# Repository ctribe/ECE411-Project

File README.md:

The nocLock
==============

A secret knock detector for you to hide your everyday items!

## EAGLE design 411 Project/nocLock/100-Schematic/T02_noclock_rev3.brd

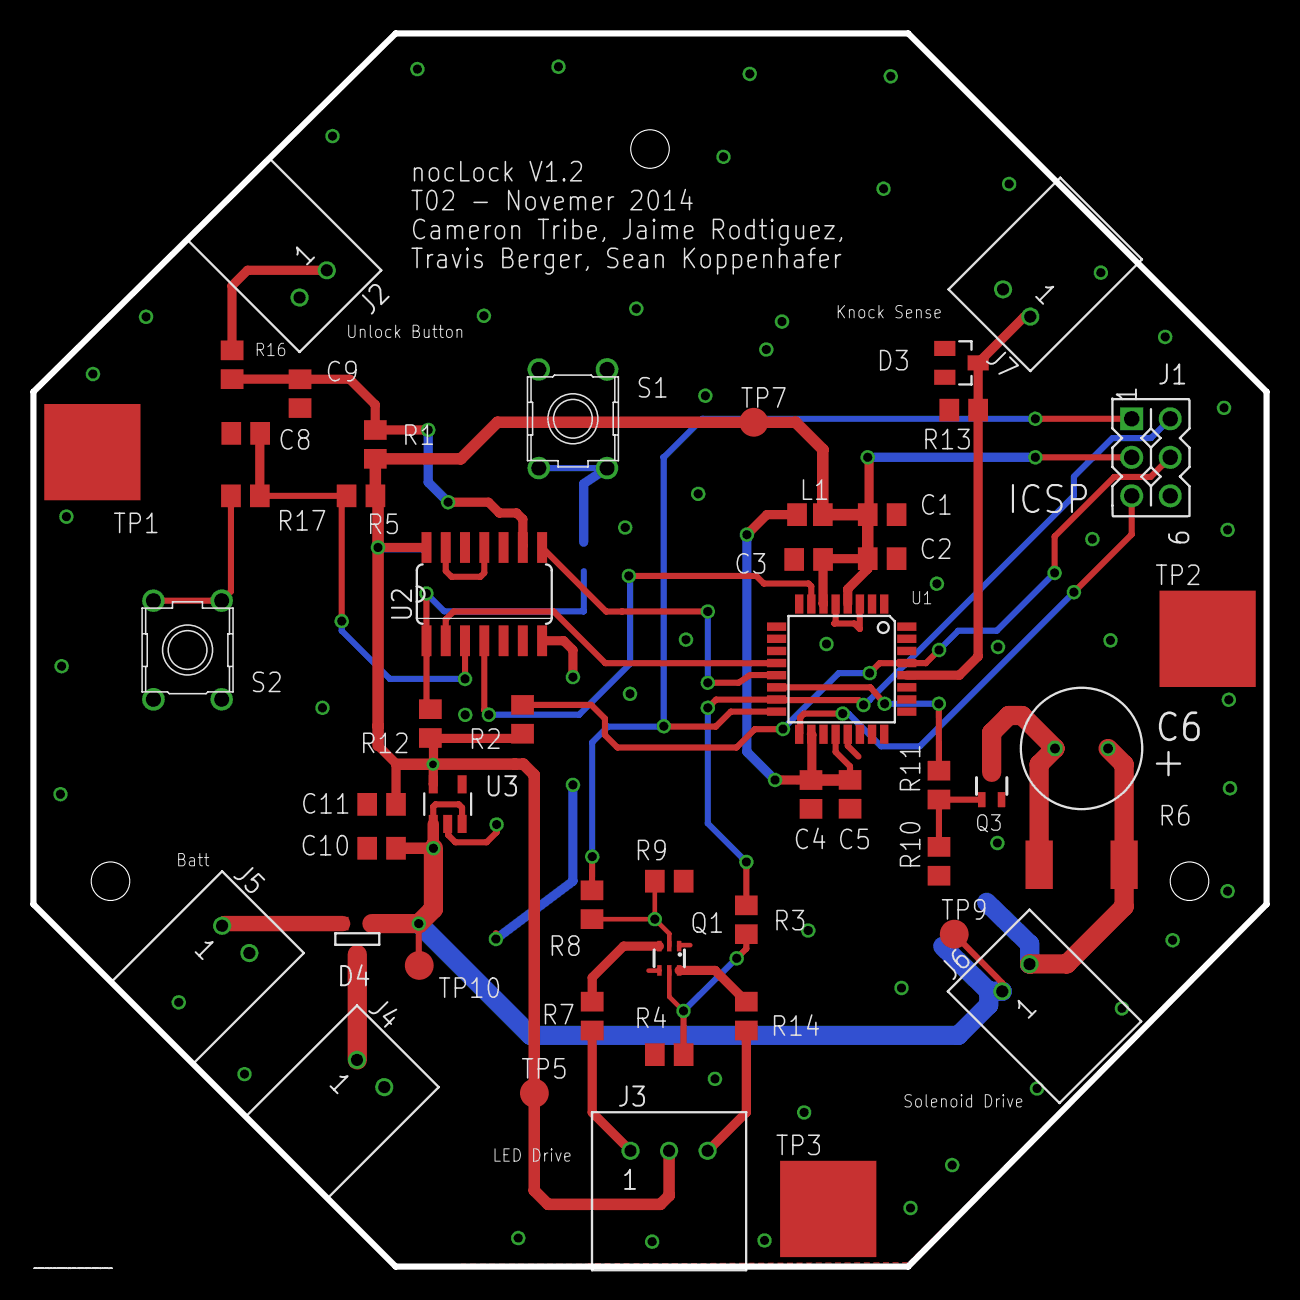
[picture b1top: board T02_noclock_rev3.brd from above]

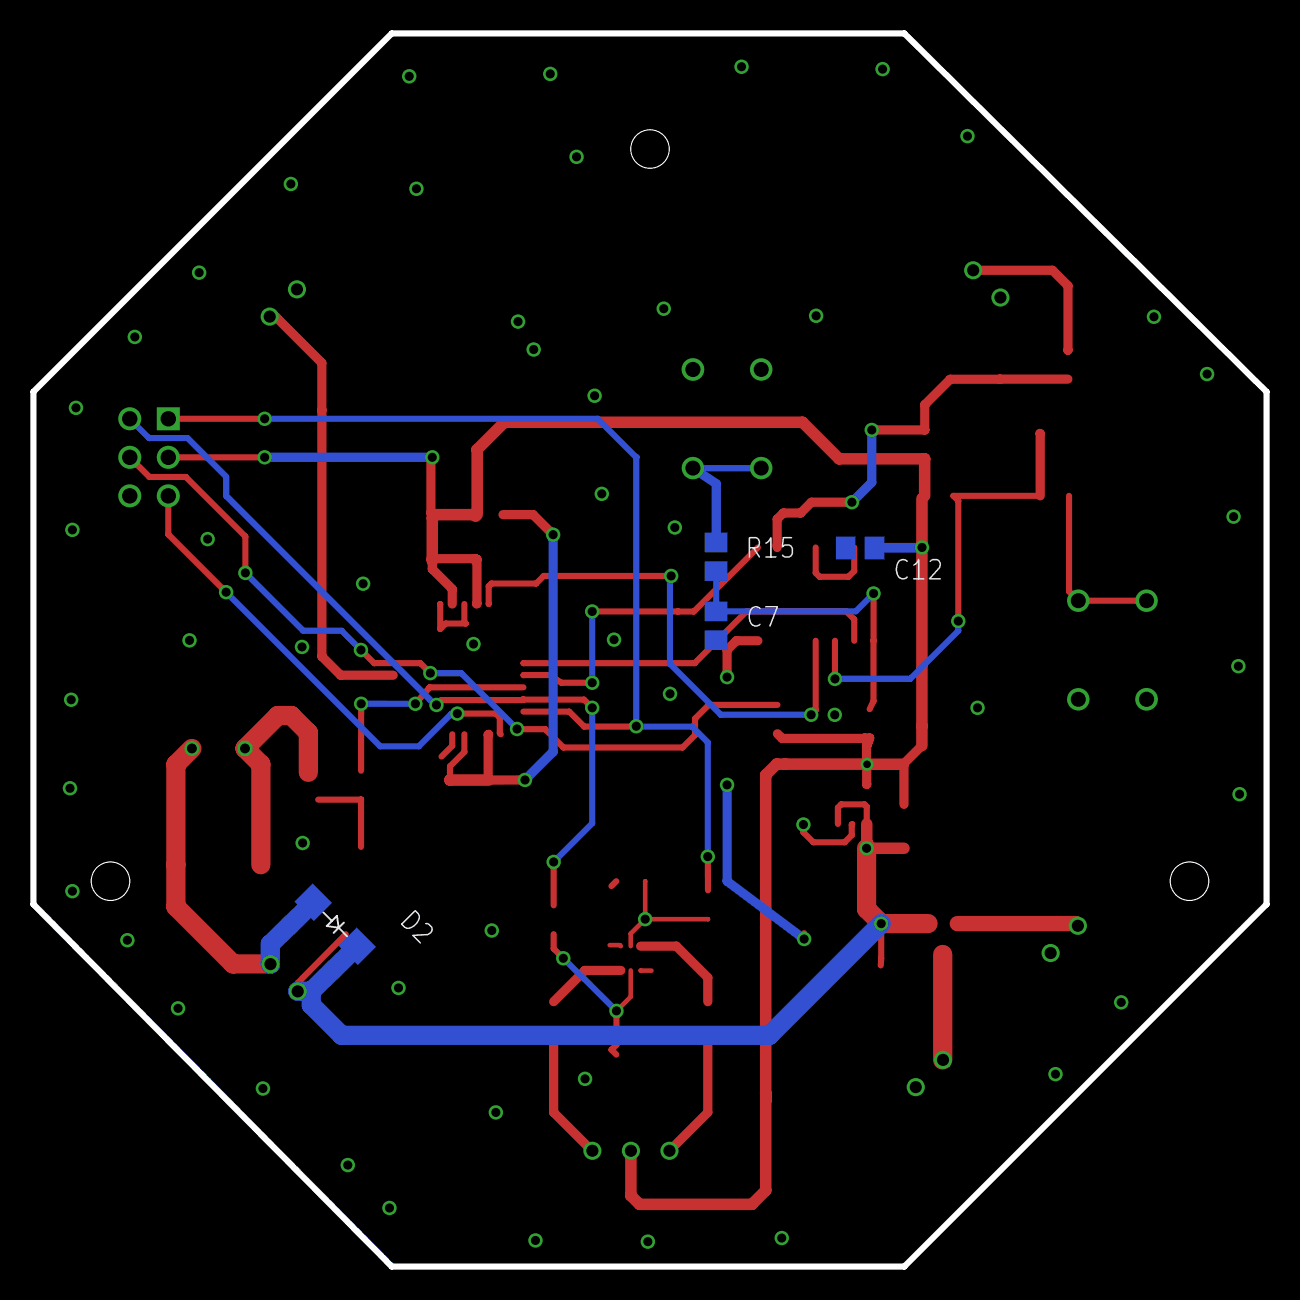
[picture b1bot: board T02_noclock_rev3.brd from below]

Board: 2 copper layers, 81.3 x 81.3 mm, 54 parts (4 on the bottom side), 30 nets.

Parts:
C1, C5: 4.7uF; C0805
C2, C3, C4: 0.1uF; C0805
C6: 1000uF; EKY-100ELL102MH20D
C7, C8, C9, C10, C11, C12: 1uF; C0805
D2: GF1; SMA-DO214AC
D3: 5.1V; SOT23
D4: PMEG2005CT,215; SOT-23
J1: ICSP
J2, J4, J5, J6, J7: 640455-2; 2-PIN_CONNECTOR
J3: 5BC-3-CA-F; 3_PIN_CONNECTOR
L1: CE201210-10NJ; R0805
Q1: DMN63D8LDW-7; SOT363
Q3: DMG1012UW-7; SOT323
R1, R2, R4, R9: 10K; R0805
R3, R8, R11: 1k; R0805
R5, R10, R12: 10k; R0805
R6: 10; R2512
R7: 330; R0805
R13: 1M; R0805
R14: 220; R0805
R15, R16, R17: 100; R0805
S1, S2: 2-1825910-7; FSM14JH
TP1, TP2, TP3: TP; TP100SQ
TP5, TP7, TP9, TP10: TPTP19R; TP19R
U1: ATMEGA88A; TQFP32
U2: 4584D; SO14
U3: MCP1802; SOT23-5

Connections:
9V: D4.3, J4.1
+5V: C1.1, C2.1, C3.1, C11.1, C12.1, J1.2, J3.2, L1.2, R1.1, R2.1, R5.1, R12.1, TP5.TP, TP7.TP, U1.4, U1.6, U2.14, U3.5
+9V: C10.1, D2.K, D4.2, J6.1, TP9.TP, TP10.TP, U3.1, U3.3
AVCC: C4.1, C5.1, L1.1, U1.18, U1.20
BATT: D4.1, J5.1
GND: C1.2, C2.2, C3.2, C4.2, C5.2, C7.2, C8.2, C9.2, C10.2, C11.2, C12.2, D3.1, J1.6, J2.2, J4.2, J5.2, J7.2, Q1.S1, Q1.S2, Q3.3, R4.1, R9.1, R10.1, R13.2, S1.1, S1.2, S2.1, S2.2, TP1.P$1, TP2.P$1, TP3.P$1, U1.3, U1.5, U1.21, U2.7, U2.11, U2.13, U3.2
KNOCK_SENSE: D3.3, J7.1, R13.1, U1.28
MISO: J1.1, R8.2, U1.16
MOSI: J1.4, R3.2, U1.15
unnamed: Q1.D1, R7.1
unnamed: Q1.G2, R8.1, R9.2
unnamed: C9.1, R1.2, R16.2, U2.9
unnamed: U1.7, U2.4
unnamed: J3.1, R7.2
unnamed: J3.3, R14.2
unnamed: R15.1, S1.3, S1.4
unnamed: Q1.D2, R14.1
unnamed: Q3.2, R10.2, R11.1
unnamed: C6.+, D2.A, J6.2, R6.2
unnamed: C6.-, Q3.1, R6.1
unnamed: R17.1, S2.3, S2.4
unnamed: C8.1, R5.2, R17.2, U2.3
unnamed: J2.1, R16.1
unnamed: C7.1, R12.2, R15.2, U2.1
unnamed: Q1.G1, R3.1, R4.2
PROGRAM: U1.12, U2.2
RESET: J1.5, R2.2, U1.29
SCK: J1.3, U1.17
SOLENOID_CONTROL: R11.2, U1.14
UNLOCK: U1.13, U2.8

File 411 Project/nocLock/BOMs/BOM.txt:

Partlist exported from /Users/Jrodriguez/Documents/ECE411-Project/411 Project/nocLock/100-Schematic/T02_noclock_rev3.sch at 10/31/14 4:01 PM

Qty Value          Device           Package         Parts                     Description                          PARTNUM            TP_SIGNAL_NAME
3   0.1uF          C-EUC0805        C0805           C2, C3, C4                CAPACITOR, European symbol           GRM155R61A104KA01D               
1   10             R-US_R2512       R2512           R6                        RESISTOR, American symbol            CRM2512-JW-100ELF                
3   100            R-US_R0805       R0805           R15, R16, R17             RESISTOR, American symbol            ESR10EZPJ103                     
1   1000uF         CPOL-US          3.5MM_8MM       C6                        POLARIZED CAPACITOR, American symbol EKY-100ELL102MH20D               
4   10K            R-US_R0805       R0805           R1, R2, R4, R9            RESISTOR, American symbol            ESR10EZPJ103                     
3   10k            R-US_R0805       R0805           R5, R10, R12              RESISTOR, American symbol            ESR10EZPJ103                     
1   10nH           L-USL0805        R0805           L1                        INDUCTOR, American symbol            CE201210-10NJ                    
1   1M             R-US_R0805       R0805           R13                       RESISTOR, American symbol            RMCF0805JT1M00                   
3   1k             R-US_R0805       R0805           R3, R8, R11               RESISTOR, American symbol            MCR10ERTF1001                    
6   1uF            C-EUC0805        C0805           C7, C8, C9, C10, C11, C12 CAPACITOR, European symbol           CL21B105KBFNNNE                  
1   220            R-US_R0805       R0805           R14                       RESISTOR, American symbol            RMCF0805FT220R                   
1   330            R-US_R0805       R0805           R7                        RESISTOR, American symbol            MCR10ERTF3300                    
2   4.7uF          C-EUC0805        C0805           C1, C5                    CAPACITOR, European symbol           CL21A475KOFNNNE                  
1   4584D          4584D            SO14            U2                        Hex SCHMITT TRIGGER (74C14)          4584D                            
1   5.1V           ZENER-DIODESOT23 SOT23           D3                        Z-Diode                              BZX84C4V7-TP                     
1   5BC-3-CA-F     5BC-3-CA-F       3_PIN_CONNECTOR J3                        Connector Recept, 3-Pin              5BC-3-CA-F                       
5   640455-2       640455-2         2-PIN_CONNECTOR J4, J5, J6, J7, J8        2 Pin Rectangular Connector          640455-2                         
1   ATMEGA88A      ATMEGA88A        TQFP32          U1                        ATMega88A                            ATMEGA88A-AUR                    
1   DMG1012UW-7    DMG1012UW-7      SOT323          Q3                        MOSFET N-CH 20V 1A SOT323            DMG1012UW-7                      
1   DMN63D8LDW-7   DMN63D8LDW-7     SOT363          Q1                        Dual MOSFET 2N-CH 30V 220MA SOT363   DMN63D8LDW-7                     
1   GF1            GF1              SMA-DO214AC     D2                        DIODE                                S1J                              
1   ICSP           ICSP             ICSP            J1                        Programming ICSP Header              PRPC012DAANRC                    
1   MCP1802        MCP1802          SOT23-5         U3                        5V Voltage Regulator MCP1802         MCP1802                          
1   PMEG2005CT,215 PMEG2005CT,215   SOT-23          D4                                                             PMEG2005CT,215                   
1   SKHMPSE010     SKHMPSE010       SKHMPXE010      S2                        6.2 X 6.5mm TACT Switch (SMD)                                         
1   TPTP19R        TPTP19R          TP19R           TP1                       Test pad

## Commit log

2014-10-06 Inital code that hasn't been debugged yet
2014-10-08 Changed timer to work with 8MHz clock and added eeprom knock storage
2014-10-08 Updated comment about timer resolution
2014-10-08 Jaime
    Added Project folders
2014-10-09 added stuff
2014-10-09 Corrected documentation directories.
2014-10-10 Corrected directory issues
2014-10-10 Added homework 2 and moved nocLock.c to Software.
2014-10-12 Updated Requirements and added datasheet.
    This darlington pair can be used instead of the TIP112. Its cheaper and
    it can be sold in a SMT package.
2014-10-12 Updated BOM with major components.
    I also added all appropriate data sheets to the data sheets folder.
2014-10-12 Added more datasheets and updated BOM
2014-10-13 Jaime
    Added Schematic
2014-10-13 Small update to read eeprom and added simulation branch
2014-10-13 erased
2014-10-13 Added legacy version of BOM
2014-10-14 Added task list folder and file.
2014-10-14 UART enabled for TX
2014-10-15 Eagle Library
2014-10-15 Case design
2014-10-15 jaime
2014-10-15 Added lib and edited BOM
2014-10-15 Updated BOM
2014-10-15 Updated Eagle lib
2014-10-15 Added ATMega88A to nocLock_lbr
2014-10-17 added more components to library.
2014-10-17 schematic change
2014-10-17 library debug
2014-10-17 Restarted lib
2014-10-19 Updated schematics, added parts to library.
2014-10-19 Updated schematic
2014-10-20 Added parts - Jaime
2014-10-20 Updated Schematics
2014-10-20 Working Version after Debug
2014-10-20 Created Library for Voltage Regulator
2014-10-20 Added schematic parts
    fixed LED common anode
    new connector added
    updated BOM
2014-10-21 lock description-jaime
2014-10-23 Updated Schematics with additional circuitry.
2014-10-23 Implemented new nocLock feature set. Spun new version
2014-10-23 Jaime
    Finished schematic and updated Library
2014-10-25 Created WPR Folder added first WPR
2014-10-25 Added my weekly progress report
2014-10-25 Requirements Doc Rev 1
2014-10-26 updated Library
2014-10-26 Updated WPR
    Changed due date to Sunday.
2014-10-26 WPR Update
    Changed WPR To 10/26.
2014-10-26 Revert "Updated WPR"
    This reverts commit 3cfb1aeb726932070d7e07aaba60c330598cb72d.
2014-10-26 Revert "WPR Update"
    This reverts commit bc0b64a98f160310f7076dc2b64158c707fdb378.
2014-10-26 Change
2014-10-26 Debugged and got the code working
2014-10-26 Updated schematics and library
2014-10-26 removed WPR folder
2014-10-26 Remove simulation branch of software
2014-10-26 Changed WPR
2014-10-27 Formatted and edited requirements document.
2014-10-27 Uploaded weekly report.
2014-10-27 Updated
    Project requirements
    added WPR
2014-10-27 Finalized Requirements Document
2014-10-28 added connectors
2014-10-29 Started Board Layout
2014-10-29 added deleted files
2014-10-29 Added App Note
2014-10-30 Updated Schematic and Library
    added part numbers to all parts as attributes.
2014-10-31 Debug timing issues and compare issues
2014-11-01 Updated BOM for digikey order.
2014-11-01 Sean WPR
2014-11-01 Updated WPR
2014-11-03 Submitted PCB Rev 3
2014-11-03 Added WPR for this week.
2014-11-03 Fix schematic error.
2014-11-03 LATEST FILES
2014-11-03 Added +9V to part lib
2014-11-04 Revised PCB layout.
    Some work still needs to be done. Figure out a 5V power place rather
    than a single trace to all things 5V.
2014-11-05 Board revision
    Fixed various issues with current layout, aded logo, and team name.
2014-11-05 Fixing Schematic Error
2014-11-05 Added good PCB and sch file
2014-11-07 Updated WRP directory.
2014-11-07 Removed Hash files
2014-11-07 Rerouted EEPROM reset to PB6
2014-11-07 Active high buttons
2014-11-10 Submitted WPR 11/9
2014-11-10 Added gerbers, added WPR, updated pcb logo
2014-11-10 Edited WPR
2014-11-10 Updated software documentation
2014-11-10 Updated directories.
2014-11-10 Committed Project Requirements
    Pushed Rev 2.0
    Pushed Rev 3.0
    Changed Folder Directory
2014-11-10 fix git
2014-11-10 fixing git
2014-11-10 Updated Folder Directory for Requirements
2014-11-10 Updated Project Schedule
    Added Project Schedule Folder
    Committed Rev 2.0/3.0
2014-11-14 Added New Directory for new HW assignment.
    Also Added block diagrams for the HW assignment
2014-11-14 State diagram for homework
2014-11-14 added description tables for block diagram.
2014-11-15 Fixed corrupt board file.
2014-11-15 Created PCB Errors document
2014-11-16 Updated documentation
    Modified Block diagrams and descriptions. Added another error to the
    PCB errors document.
2014-11-16 Added WPR
2014-11-17 Revert "Sean WPR"
    This reverts commit fd52fd683741aab9c602311b7edf3c9784593db7.
2014-11-17 Revert "fixing git"
    This reverts commit b19157635f1bddf96b37074ee97dd971ba43d72b.
2014-11-17 fixed git
2014-11-17 Completed Description Table
2014-11-17 Added more orders.
2014-11-17 HW5 -Jaime
2014-11-17 Jaime HW5 V1.1
2014-11-17 HW5 System Design
2014-11-21 Add my test stuff
2014-11-22 Full software test case
2014-11-23 Removed unnecessary files, Added solenoid test doc
2014-11-23 Added week 5 for WPRs
2014-11-23 Edited Solenoid Test Case
2014-11-23 Added Test Plan Rev 1.0
2014-11-24 Updated Test Plan
2014-11-24 Updated my unit test
2014-11-24 Berger WPR
2014-11-24 Grammar
2014-11-24 Added Test Case 4.1
2014-11-24 Added Test Plan 2.0
2014-11-24 Updated Test cases 4.1/7.1
2014-11-24 Updated Test Case 7.1 / 1.7
2014-11-24 Updated Test Case 1.2
2014-11-24 Updated Test Plan document
2014-11-27 Now blinks RED when a program combination fails to match
2014-11-28 User manual
2014-12-01 Sean WPR 11/30
2014-12-01 WPR-Jaime
2014-12-01 added drawing for lock box
2014-12-05 Changed button delay for outside button
2014-12-05 WPR 11_30
2014-12-05 WPR Folder Change
2014-12-05 Submitted my WPR
2014-12-05 Software presentation
2014-12-05 Added PCB Enclosure Drawing
2014-12-06 Pdf of software presentation
2014-12-10 Revert "Pdf of software presentation"
    This reverts commit b65a2823dc69437b96063dcc82908c6a76351c92.
2014-12-10 Presentation
2014-12-10 Jaime presentation
2014-12-10 Added draft for presentation
2014-12-11 UPDATED PRESENTATION
2014-12-11 Uploaded Presentation
2014-12-11 Updated BOM and cleansed up directories.
2014-12-12 Changed delay after knock and tolerance for the knock acceptance window
2014-12-12 Cleaned up files and updated presentation
